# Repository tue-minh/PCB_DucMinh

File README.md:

<div align="center">
  
  <p style="margin-top: 10px; color: #555; font-size: 0.9em; font-style: italic;">
    🔍 <b>Fig.</b> Hardware Review.
  </p>
</div>

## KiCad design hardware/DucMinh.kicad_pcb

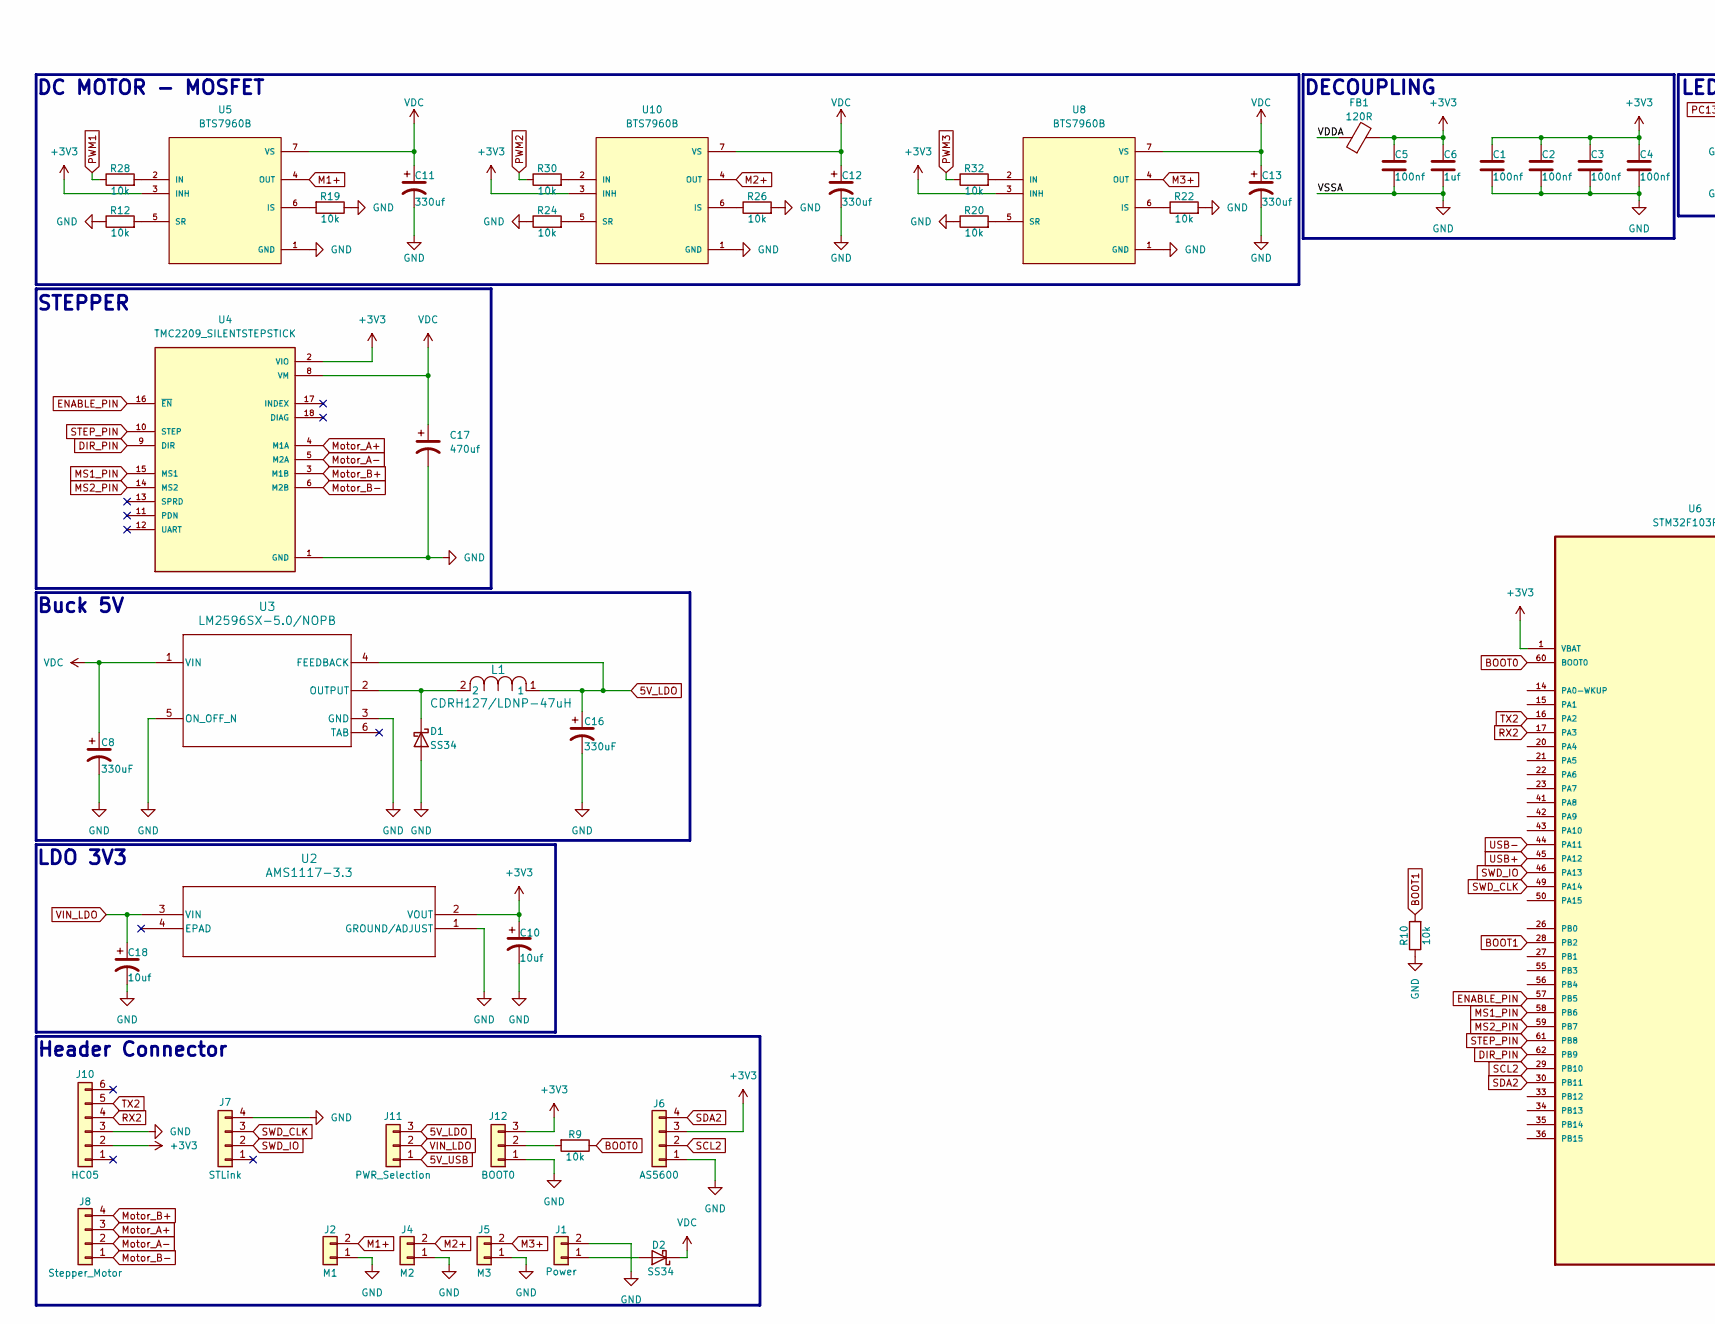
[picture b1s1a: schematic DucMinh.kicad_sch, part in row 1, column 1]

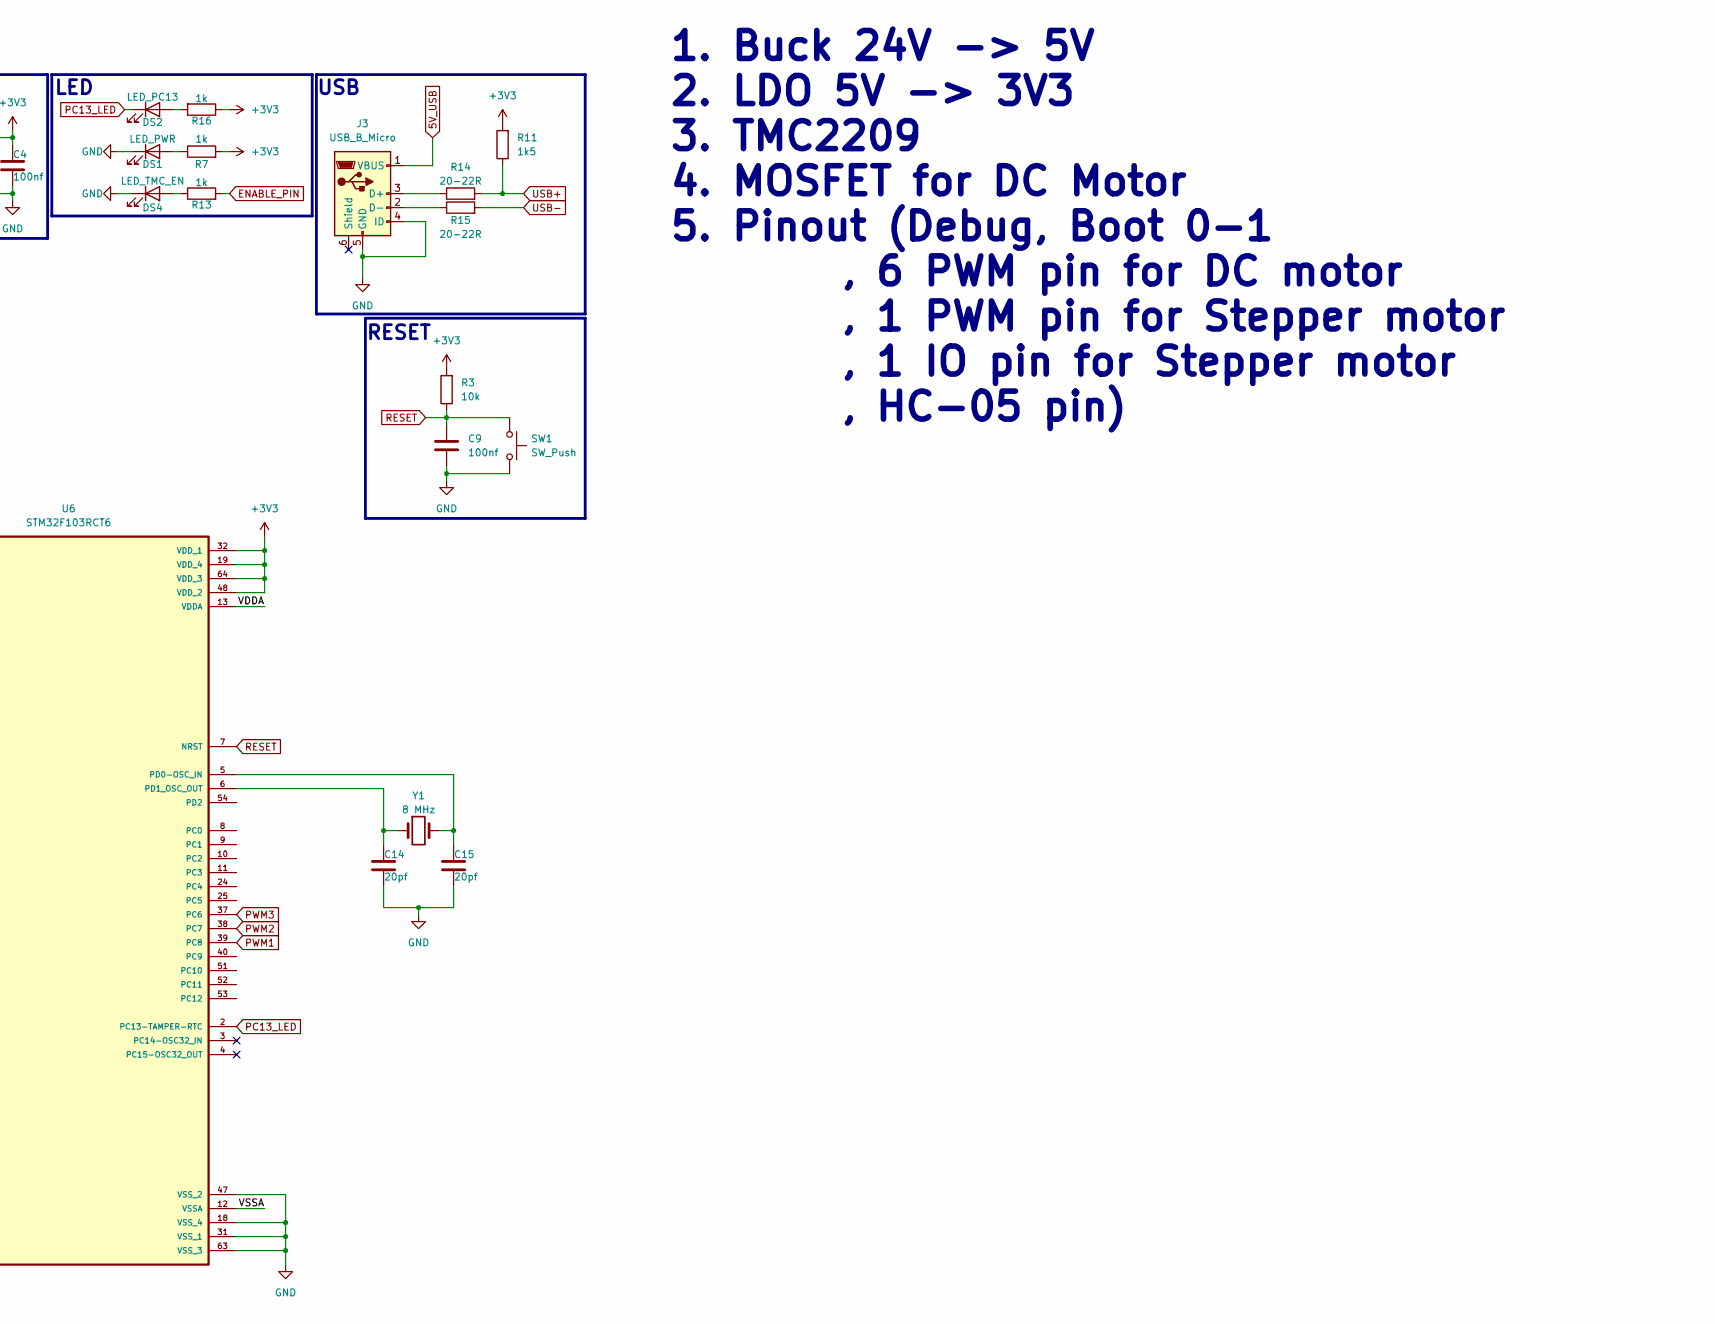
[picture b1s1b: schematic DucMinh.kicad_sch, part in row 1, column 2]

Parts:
C1, C2, C3, C4, C5, C9: 100nf; C_0603_1608Metric_Pad1.08x0.95mm_HandSolder
C6: 1uf; C_0603_1608Metric_Pad1.08x0.95mm_HandSolder
C8, C16: 330uF; CP_Radial_D8.0mm_P5.00mm
C10, C18: 10uf; tue_tantalum_6032
C11, C12, C13: 330uf; CP_Radial_D8.0mm_P5.00mm
C14, C15: 20pf; C_0603_1608Metric_Pad1.08x0.95mm_HandSolder
C17: 470uf; CP_Radial_D8.0mm_P5.00mm
D1, D2: SS34; D_SMA
DS1: LED_PWR; LED_0603_1608Metric_Pad1.05x0.95mm_HandSolder
DS2: LED_PC13; LED_0603_1608Metric_Pad1.05x0.95mm_HandSolder
DS4: LED_TMC_EN; LED_0603_1608Metric_Pad1.05x0.95mm_HandSolder
FB1: 120R; R_0603_1608Metric
J1: Power; TerminalBlock_bornier-2_P5.08mm
J2: M1; TerminalBlock_bornier-2_P5.08mm
J3: USB_B_Micro; USB_Micro-B_Amphenol_10118193-0001LF_Horizontal
J4: M2; TerminalBlock_bornier-2_P5.08mm
J5: M3; TerminalBlock_bornier-2_P5.08mm
J6: AS5600; PinHeader_1x04_P2.54mm_Vertical
J7: STLink; PinHeader_1x04_P2.54mm_Vertical
J8: Stepper_Motor; JST_XH_B4B-XH-A_1x04_P2.50mm_Vertical
J10: HC05; PinHeader_1x06_P2.54mm_Vertical
J11: PWR_Selection; tue_SS12D00_3P_2.5mm
J12: BOOT0; tue_SS12D00_3P_2.5mm
L1: CDRH127/LDNP-47uH; tue__CDRH127LDNP-470MC_SUM
R3, R9, R10, R12, R19, R20, R22, R24, R26, R28, R30, R32: 10k; R_0603_1608Metric_Pad0.98x0.95mm_HandSolder
R7, R13, R16: 1k; R_0603_1608Metric_Pad0.98x0.95mm_HandSolder
R11: 1k5; R_0603_1608Metric_Pad0.98x0.95mm_HandSolder
R14, R15: 20-22R; R_0603_1608Metric_Pad0.98x0.95mm_HandSolder
SW1: SW_Push; SW_PUSH_6mm
U2: AMS1117-3.3; SOT_AMS_ADS
U3: LM2596SX-5.0/NOPB; tue_lm2596
U4: TMC2209_SILENTSTEPSTICK; tue_TMC2209; PARTREV 1.20
U5, U8, U10: BTS7960B; DPAK127P1490X440-8N; PARTREV 1.1
U6: STM32F103RCT6; QFP50P1200X1200X160-64N
Y1: 8 MHz; Crystal_HC49-4H_Vertical

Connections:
5V_LDO: C16.1, J11.3, L1.1, U3.4 (FEEDBACK)
5V_USB: J3.1 (VBUS), J11.1
+3V3: C1.1, C2.1, C3.1, C4.1, C5.1, C6.1, C10.1, FB1.2, J6.3, J10.2, J12.3, R3.2, R7.2, R11.2, R16.1, U2.2 (VOUT), U4.2 (VIO), U5.3 (INH), U6.1 (VBAT), U6.19 (VDD_4), U6.32 (VDD_1), U6.48 (VDD_2), U6.64 (VDD_3), U8.3 (INH), U10.3 (INH)
/VDDA: FB1.1, U6.13 (VDDA)
BOOT0: R9.1, U6.60 (BOOT0)
BOOT1: R10.2, U6.28 (PB2)
DIR_PIN: U4.9 (DIR), U6.62 (PB9)
ENABLE_PIN: R13.2, U4.16 (~EN), U6.57 (PB5)
GND: C1.2, C2.2, C3.2, C4.2, C5.2, C6.2, C8.2, C9.2, C10.2, C11.2, C12.2, C13.2, C14.2, C15.2, C16.2, C17.2, C18.2, D1.2 (A), DS1.1 (K), DS4.1 (K), J1.2, J2.1, J3.4 (ID), J3.5 (GND), J4.1, J5.1, J6.1, J7.4, J10.3, J12.1, R10.1, R12.1, R19.1, R20.1, R22.2, R24.1, R26.2, SW1.2, U2.1 (GROUND/ADJUST), U3.3 (GND), U3.5 (ON_OFF_N), U4.1 (GND), U4.7 (GND), U5.1 (GND), U6.12 (VSSA), U6.18 (VSS_4), U6.31 (VSS_1), U6.47 (VSS_2), U6.63 (VSS_3), U8.1 (GND), U10.1 (GND)
M1+: J2.2, U5.4 (OUT), U5.8 (OUT)
M2+: J4.2, U10.4 (OUT), U10.8 (OUT)
M3+: J5.2, U8.4 (OUT), U8.8 (OUT)
MS1_PIN: U4.15 (MS1), U6.58 (PB6)
MS2_PIN: U4.14 (MS2), U6.59 (PB7)
Motor_A+: J8.3, U4.4 (M1A)
Motor_A-: J8.2, U4.5 (M2A)
Motor_B+: J8.4, U4.3 (M1B)
Motor_B-: J8.1, U4.6 (M2B)
unnamed: D1.1 (K), L1.2, U3.2 (OUTPUT)
unnamed: D2.2 (A), J1.1
unnamed: DS1.2 (A), R7.1
unnamed: DS2.2 (A), R16.2
unnamed: DS4.2 (A), R13.1
unnamed: J3.3 (D+), R14.1
unnamed: J3.2 (D-), R15.1
unnamed: J12.2, R9.2
unnamed: R28.2, U5.2 (IN)
unnamed: R19.2, U5.6 (IS)
unnamed: R12.2, U5.5 (SR)
unnamed: C15.1, U6.5 (PD0-OSC_IN), Y1.2
unnamed: C14.1, U6.6 (PD1_OSC_OUT), Y1.1
unnamed: R32.2, U8.2 (IN)
unnamed: R22.1, U8.6 (IS)
unnamed: R20.2, U8.5 (SR)
unnamed: R30.2, U10.2 (IN)
unnamed: R26.1, U10.6 (IS)
unnamed: R24.2, U10.5 (SR)
PC13_LED: DS2.1 (K), U6.2 (PC13-TAMPER-RTC)
PWM1: R28.1, U6.39 (PC8)
PWM2: R30.1, U6.38 (PC7)
PWM3: R32.1, U6.37 (PC6)
RESET: C9.1, R3.1, SW1.1, U6.7 (NRST)
RX2: J10.4, U6.17 (PA3)
SCL2: J6.2, U6.29 (PB10)
SDA2: J6.4, U6.30 (PB11)
STEP_PIN: U4.10 (STEP), U6.61 (PB8)
SWD_CLK: J7.3, U6.49 (PA14)
SWD_IO: J7.2, U6.46 (PA13)
TX2: J10.5, U6.16 (PA2)
USB+: R11.1, R14.2, U6.45 (PA12)
USB-: R15.2, U6.44 (PA11)
VDC: C8.1, C11.1, C12.1, C13.1, C17.1, D2.1 (K), U3.1 (VIN), U4.8 (VM), U5.7 (VS), U8.7 (VS), U10.7 (VS)
VIN_LDO: C18.1, J11.2, U2.3 (VIN)

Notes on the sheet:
DECOUPLING
Buck 5V
LDO 3V3
RESET
STEPPER
Header Connector
1. Buck 24V -> 5V 2. LDO 5V -> 3V3 3. TMC2209 4. MOSFET for DC Motor 5. Pinout (Debug, Boot 0-1 , 6 PWM pin for DC motor , 1 PWM pin for Stepper motor , 1 IO pin for Stepper motor , HC-05 pin)
DC MOTOR - MOSFET
LED
USB

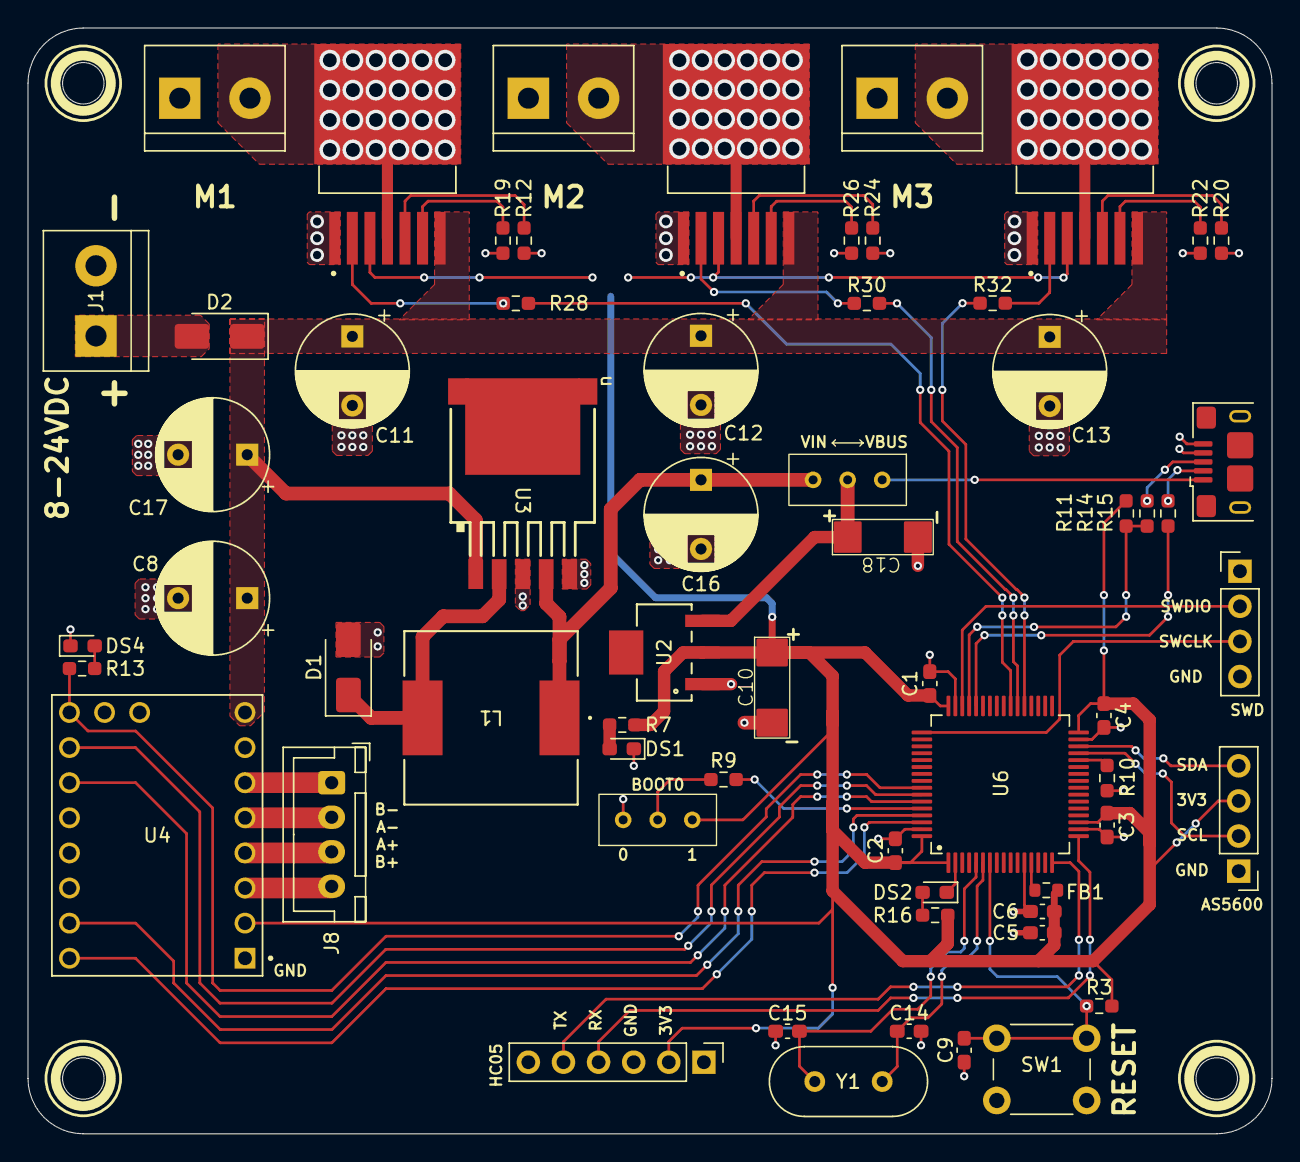
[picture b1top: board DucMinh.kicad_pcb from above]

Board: 2 copper layers, 90.0 x 80.0 mm, 62 parts (0 on the bottom side), 53 nets.

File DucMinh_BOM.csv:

Reference,Value,Footprint,Qty,,
"C1,C2,C3,C4,C5,C9",100nf,Capacitor_SMD:C_0603_1608Metric_Pad1.08x0.95mm_HandSolder,6,Có s?n,
C6,1uf,Capacitor_SMD:C_0603_1608Metric_Pad1.08x0.95mm_HandSolder,1,,
"C8,C16",330uF,Capacitor_THT:CP_Radial_D8.0mm_P5.00mm,2,,
"C10,C18",10uf,tue_tantalum6032:tue_tantalum_6032,2,Thi?u,
"C11,C12,C13",330uf,Capacitor_THT:CP_Radial_D8.0mm_P5.00mm,3,,
"C14,C15",20pf,Capacitor_SMD:C_0603_1608Metric_Pad1.08x0.95mm_HandSolder,2,Có s?n,
C17,470uf,Capacitor_THT:CP_Radial_D8.0mm_P5.00mm,1,Thi?u,
"D1,D2",SS34,Diode_SMD:D_SMA,2,,
DS1,LED_PWR,LED_SMD:LED_0603_1608Metric_Pad1.05x0.95mm_HandSolder,1,Có s?n,
DS2,LED_PC13,LED_SMD:LED_0603_1608Metric_Pad1.05x0.95mm_HandSolder,1,,
DS4,LED_TMC_EN,LED_SMD:LED_0603_1608Metric_Pad1.05x0.95mm_HandSolder,1,,
FB1,120R,Resistor_SMD:R_0603_1608Metric,1,,
J1,Power,tue_TerminalBlock:TerminalBlock_bornier-2_P5.08mm,1,,
J2,M1,tue_TerminalBlock:TerminalBlock_bornier-2_P5.08mm,1,,
J3,USB_B_Micro,Connector_USB:USB_Micro-B_Amphenol_10118193-0001LF_Horizontal,1,,
J4,M2,tue_TerminalBlock:TerminalBlock_bornier-2_P5.08mm,1,,
J5,M3,tue_TerminalBlock:TerminalBlock_bornier-2_P5.08mm,1,,
J6,AS5600,Connector_PinHeader_2.54mm:PinHeader_1x04_P2.54mm_Vertical,1,,
J7,STLink,Connector_PinHeader_2.54mm:PinHeader_1x04_P2.54mm_Vertical,1,,
J8,Stepper_Motor,Connector_JST:JST_XH_B4B-XH-A_1x04_P2.50mm_Vertical,1,,
J10,HC05,Connector_PinHeader_2.54mm:PinHeader_1x06_P2.54mm_Vertical,1,,
J11,PWR_Selection,tue_switch-SS12D00:tue_SS12D00_3P_2.5mm,1,Thi?u,
J12,BOOT0,tue_switch-SS12D00:tue_SS12D00_3P_2.5mm,1,,
L1,CDRH127/LDNP-47uH,tue_inductor_smd:tue__CDRH127LDNP-470MC_SUM,1,,
"R3,R9,R10,R12,R19,R20,R22,R24,R26,R28,R30,R32",10k,Resistor_SMD:R_0603_1608Metric_Pad0.98x0.95mm_HandSolder,12,Có s?n,
"R7,R13,R16",1k,Resistor_SMD:R_0603_1608Metric_Pad0.98x0.95mm_HandSolder,3,,
R11,1k5,Resistor_SMD:R_0603_1608Metric_Pad0.98x0.95mm_HandSolder,1,,
"R14,R15",20-22R,Resistor_SMD:R_0603_1608Metric_Pad0.98x0.95mm_HandSolder,2,,
SW1,SW_Push,Button_Switch_THT:SW_PUSH_6mm,1,,
U2,AMS1117-3.3,tue_ams1117:SOT_AMS_ADS,1,Thi?u,
U3,LM2596SX-5.0/NOPB,tue_lm2596hvs:tue_lm2596,1,,
U4,TMC2209_SILENTSTEPSTICK,tue_TMC2209:tue_TMC2209,1,,
"U5,U8,U10",BTS7960B,tue_bts7960b:DPAK127P1490X440-8N,3,,
U6,STM32F103RCT6,tue_stm32f103rct6:QFP50P1200X1200X160-64N,1,,
Y1,8 MHz,Crystal:Crystal_HC49-4H_Vertical,1,,

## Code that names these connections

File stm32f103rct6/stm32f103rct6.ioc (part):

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Mcu.Name=STM32F103R(C-D-E)Tx
Mcu.Package=LQFP64
Mcu.UserName=STM32F103RCTx
PA11.Mode=Device
PA11.Signal=USB_DM
PA12.Mode=Device
PA12.Signal=USB_DP
PA13.Mode=Serial_Wire
PA13.Signal=SYS_JTMS-SWDIO
PA14.Mode=Serial_Wire
PA14.Signal=SYS_JTCK-SWCLK
PB5.GPIOParameters=GPIO_Label
PB5.GPIO_Label=STEP_EN
PB5.Signal=GPIO_Output
PB6.GPIOParameters=GPIO_Label
PB6.GPIO_Label=STEP_MS1
PB6.Signal=GPIO_Output
PB7.GPIOParameters=GPIO_Label
PB7.GPIO_Label=STEP_MS2
PB7.Signal=GPIO_Output
PB8.GPIOParameters=GPIO_Label
PB8.GPIO_Label=STEP_PWM
PB8.Signal=S_TIM4_CH3
PB9.GPIOParameters=GPIO_Label
PB9.GPIO_Label=STEP_DIR
PB9.Signal=GPIO_Output
PC13-TAMPER-RTC.Signal=GPIO_Output
PC6.Signal=S_TIM8_CH1
PC7.Signal=S_TIM8_CH2
PC8.Signal=S_TIM8_CH3
PD0-OSC_IN.Mode=HSE-External-Oscillator
PD0-OSC_IN.Signal=RCC_OSC_IN
PD1-OSC_OUT.Mode=HSE-External-Oscillator
PD1-OSC_OUT.Signal=RCC_OSC_OUT
RCC.SYSCLKFreq_VALUE=72000000
RCC.SYSCLKSource=RCC_SYSCLKSOURCE_PLLCLK
board=custom

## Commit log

2026-02-23 fix routes
2026-03-02 add 74hct125 routes
2026-03-06 add bts7960
2026-03-07 final
2026-03-07 final2
2026-03-08 update apperance
2026-03-12 final1
2026-03-12 save pcb
2026-03-29 add step, dc motor lib software
2026-03-29 add platformio.ini config
2026-03-29 add Readme.md, fix cmd interface
2026-03-30 update image
